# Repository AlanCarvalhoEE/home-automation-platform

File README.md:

# Home Automation Platform (HAP)

A modular, self-hosted home automation platform focused on reliability, local control, and secure remote access.

The system is designed around a Raspberry Pi server that centralizes application logic and device state, ESP8266-based IoT modules for field control, and a mobile
application as the primary user interface. Communication between components is event-driven and optimized for embedded and low-latency environments.

---

## System Architecture

The platform follows a layered architecture:

- **User Interface Layer**: Mobile and web-based interfaces for monitoring and
  control.
- **Application Layer**: Centralized logic running on a Raspberry Pi server.
- **Device Layer**: Custom ESP8266-based hardware modules controlling actuators
  and sensors.

Remote access is secured using a VPN, allowing the system to remain fully functional without relying on external cloud services.

---

## Components Overview

### Mobile App / Web Interface
- Provides real-time monitoring and control of devices
- Sends user commands to the server
- Displays device states and sensor data

### Server (Raspberry Pi)
- Central application logic
- Device state management
- Local database storage
- MQTT-based device communication
- REST API for configuration and user interfaces

### IoT Devices (ESP8266)
- Custom-designed hardware modules
- Event-driven communication using MQTT
- Designed as lightweight, replaceable nodes
- Examples:
  - On/Off relay modules
  - Sensor modules
  - Air conditioner control modules

---

## Repository Structure

```
hap/
├── docs/       # Documentation, diagrams, images
├── firmware/   # ESP8266 firmware for IoT modules
├── hardware/   # PCB designs, schematics, manufacturing files
├── mobile/     # Android application
├── server/     # Core server logic and services
└── README.md
```

---

## Technology Stack

### Embedded & Hardware
- ESP8266
- C / Arduino framework
- Custom PCB design

### Server
- Raspberry Pi
- Python
- MQTT
- SQLite
- TCP/IP networking

### Mobile
- Android (Java)
- Local and remote control support

### Communication & Security
- MQTT for device communication
- REST API for configuration and UI interaction
- VPN-based secure remote access
- Local-first architecture (no cloud dependency)

---

## Communication Model

- Devices publish state changes and sensor data via MQTT
- The server processes events and applies application logic
- Commands are sent back to devices via MQTT topics
- The mobile app interacts with the server through secure API calls

---

## System Setup Steps

- Install a lightweight Raspberry Pi OS:
  - Raspberry Pi OS Lite (recommended)
  - Enable SSH during installation
  - Configure a static local IP address

- Update the system:
```
sudo apt update
sudo apt upgrade -y
```

- Install and configure GIT:
```
sudo apt install git -y
```

- Clone the repository:
```
git clone https://github.com/AlanCarvalhoEE/hap.git
```

- Enter project folder:
```
cd hap
```

- Edit your credentials:
```
cp server/scripts/credentials_example.py server/scripts/credentials.py
nano server/scripts/credentials.py
```

- Run setup.sh:
```
cd setup
chmod +x setup.sh
./setup.sh
```
  - The script will install all the needed packages, dependencies and services.

- Configure Mosquitto:
```
sudo nano /etc/mosquitto/mosquitto.conf
```
  - Include to the end of the file:
  ```
  listener 1883
  allow_anonymous true
  ```

- Restart Mosquitto:
```
sudo systemctl restart mosquitto
```

- Connect to your ZeroTier network (must be previously created on web browser):
```
sudo zerotier-cli join <network_id>
```
  - After joining, the device must be allowed on the ZeroTier network dashboard.

- Reboot the Raspberry Pi:
```
sudo reboot now
```

---

## Current Status

- Core server architecture implemented
- Custom IoT ON-OFF module developed and tested
- Core Android application implemented
- Secure remote access functional

---

## Roadmap

Planned improvements:

- New custom IoT modules development
- Formal MQTT topic and message schema documentation
- Device auto-discovery and provisioning
- Improved fault tolerance and reconnection logic
- Automated testing for server-side logic
- Expanded mobile app features and UI refinement

---

## License

This project is currently intended for personal and educational use.
Licensing details may be defined in the future.

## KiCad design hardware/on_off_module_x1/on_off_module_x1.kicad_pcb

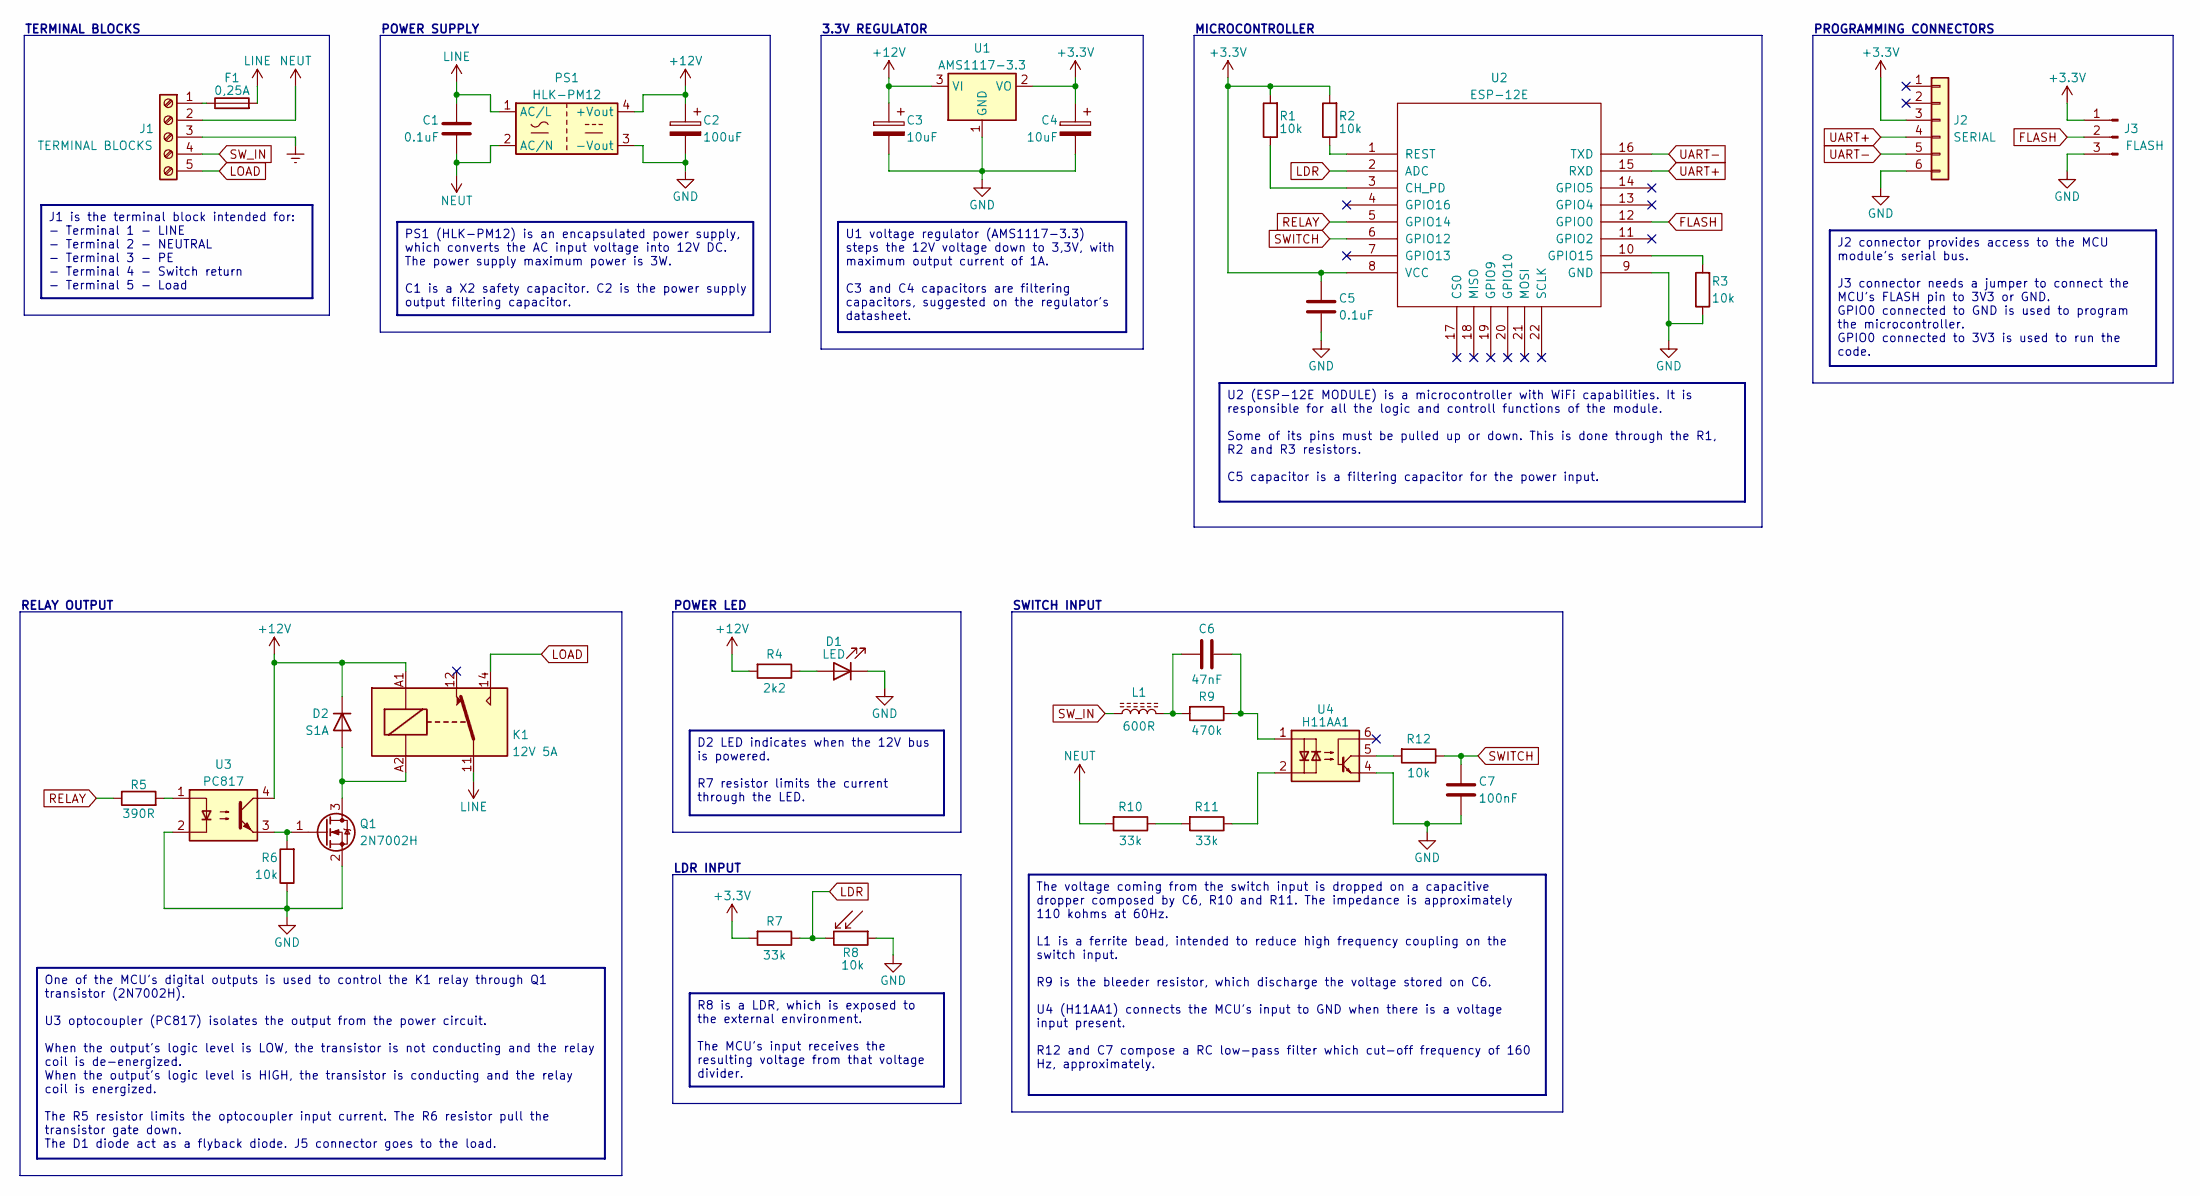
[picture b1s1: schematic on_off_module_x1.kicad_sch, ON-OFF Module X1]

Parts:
C1: 0.1uF; CAP_THT_CERAMIC_X2_18x6x15; Voltage 275V
C2: 100uF; CAP_SMD_ELEC_6.3x7.7; Voltage 16V
C3: 10uF; CAP_SMD_TANTALUM_CASE-A; Voltage 16V
C4: 10uF; CAP_SMD_TANTALUM_CASE-A; Voltage 6.3V
C5: 0.1uF; CAP_SMD_CERAMIC_0603; Voltage 6.3V
C6: 47nF; CAP_THT_CERAMIC_X2_13x5x11_P10; Voltage 350V
C7: 100nF; CAP_SMD_CERAMIC_0603; Voltage 6,3V
D1: LED; LED_SMD_0603
D2: S1A; DIODE_SMD_SMA
F1: 0,25A; FUSEHOLDER_THT_5x20_CLIP; Voltage 250V
J1: CONN_TERMINAL-BLOCK_5P_P5.08
J2: Conn_01x06_Socket; CONN_SOCKET-HEADER_1x06_V
J3: Conn_01x03_Socket; CONN_PIN-HEADER_1x03_V
K1: 12V 5A; RELAY_SPDT_FINDER_36.11
L1: 600R; BEAD_SMD_1206
PS1: HLK-PM12; HILINK_HLK-PMxx
Q1: 2N7002H; SOT-23
R1, R2, R3, R6, R12: 10k; RES_SMD_0603; Tolerance 5%
R4: 2k2; RES_SMD_0603; Tolerance 5%
R5: 390R; RES_SMD_0603; Tolerance 5%
R7: 33k; RES_SMD_0603; Tolerance 5%
R8: 10k; LDR_5_V
R9: 470k; RES_SMD_1206; Tolerance 5%
R10, R11: 33k; RES_SMD_1206; Tolerance 5%
U1: AMS1117-3.3; SOT-223-3_TAB2
U2: ESP-12E; MOD_ESP-12E
U3: PC817; SMDIP-4_7.62
U4: H11AA1; SMDIP-6_7.62

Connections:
+3.3V: C4.1, C5.2, J2.3, J3.1, R1.1, R2.1, R7.1, U1.2 (VO), U2.8 (VCC)
+12V: C2.1, C3.1, D2.1 (K), K1.A1, PS1.4 (+Vout), R4.1, U1.3 (VI), U3.4
Earth: J1.3
FLASH: J3.2, U2.12 (GPIO0)
GND: C2.2, C3.2, C4.2, C5.1, C7.2, D1.1 (K), J2.6, J3.3, PS1.3 (-Vout), Q1.2 (S), R3.2, R6.2, R8.1, U1.1 (GND), U2.9 (GND), U3.2, U4.4
LDR: R7.2, R8.2, U2.2 (ADC)
LINE: C1.1, F1.2, K1.11, PS1.1 (AC/L)
LOAD: J1.5, K1.14
NEUT: C1.2, J1.2, PS1.2 (AC/N), R10.1
unnamed: C6.1, L1.2, R9.1
unnamed: C6.2, R9.2, U4.1
unnamed: D1.2 (A), R4.2
unnamed: D2.2 (A), K1.A2, Q1.3 (D)
unnamed: F1.1, J1.1
unnamed: Q1.1 (G), R6.1, U3.3
unnamed: R5.1, U3.1
unnamed: R10.2, R11.1
unnamed: R11.2, U4.2
unnamed: R12.1, U4.5
unnamed: R1.2, U2.3 (CH_PD)
unnamed: R3.1, U2.10 (GPIO15)
unnamed: R2.2, U2.1 (REST)
RELAY: R5.2, U2.5 (GPIO14)
SWITCH: C7.1, R12.2, U2.6 (GPIO12)
SW_IN: J1.4, L1.1
UART+: J2.4, U2.15 (RXD)
UART-: J2.5, U2.16 (TXD)

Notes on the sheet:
PS1 (HLK-PM12) is an encapsulated power supply, which converts the AC input voltage into 12V DC. The power supply maximum power is 3W. C1 is a X2 safety capacitor. C2 is the power supply output filtering capacitor.
R8 is a LDR, which is exposed to the external environment. The MCU's input receives the resulting voltage from that voltage divider.
One of the MCU's digital outputs is used to control the K1 relay through Q1 transistor (2N7002H). U3 optocoupler (PC817) isolates the output from the power circuit. When the output's logic level is LOW, the transistor is not conducting and the relay coil is de-energized. When the output's logic lev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
J2 connector provides access to the MCU module's serial bus. J3 connector needs a jumper to connect the MCU's FLASH pin to 3V3 or GND. GPIO0 connected to GND is used to program the microcontroller. GPIO0 connected to 3V3 is used to run the code.
D2 LED indicates when the 12V bus is powered. R7 resistor limits the current through the LED.
U2 (ESP-12E MODULE) is a microcontroller with WiFi capabilities. It is responsible for all the logic and controll functions of the module. Some of its pins must be pulled up or down. This is done through the R1, R2 and R3 resistors. C5 capacitor is a filtering capacitor for the power input.
U1 voltage regulator (AMS1117-3.3) steps the 12V voltage down to 3,3V, with maximum output current of 1A. C3 and C4 capacitors are filtering capacitors, suggested on the regulator's datasheet.
J1 is the terminal block intended for: - Terminal 1 - LINE - Terminal 2 - NEUTRAL - Terminal 3 - PE - Terminal 4 - Switch return - Terminal 5 - Load
The voltage coming from the switch input is dropped on a capacitive dropper composed by C6, R10 and R11. The impedance is approximately 110 kohms at 60Hz. L1 is a ferrite bead, intended to reduce high frequency coupling on the switch input. R9 is the bleeder resistor, which discharge the voltage st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
PROGRAMMING CONNECTORS
RELAY OUTPUT
POWER LED
POWER SUPPLY
LDR INPUT
TERMINAL BLOCKS
SWITCH INPUT
MICROCONTROLLER
3.3V REGULATOR

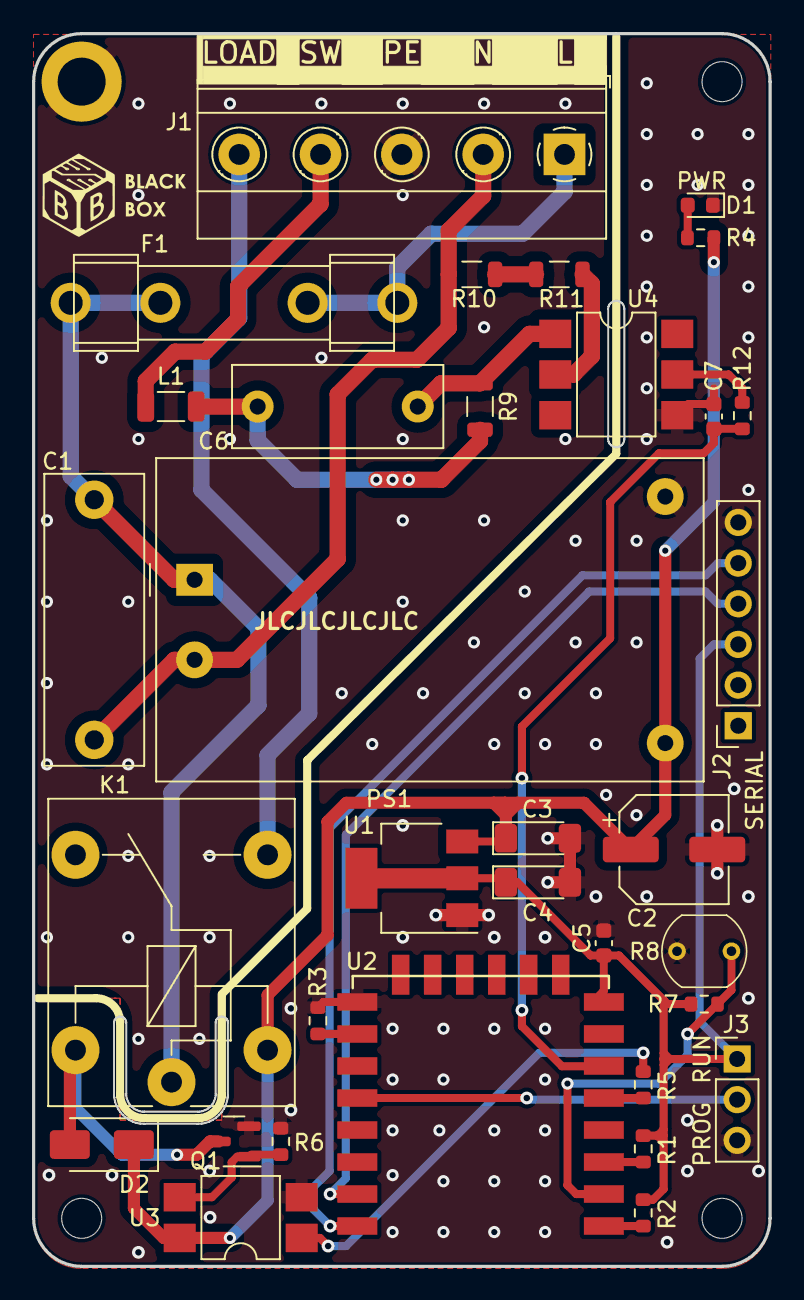
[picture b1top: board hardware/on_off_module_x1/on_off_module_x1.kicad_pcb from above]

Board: 2 copper layers, 46.0 x 77.0 mm, 33 parts (0 on the bottom side), 26 nets.

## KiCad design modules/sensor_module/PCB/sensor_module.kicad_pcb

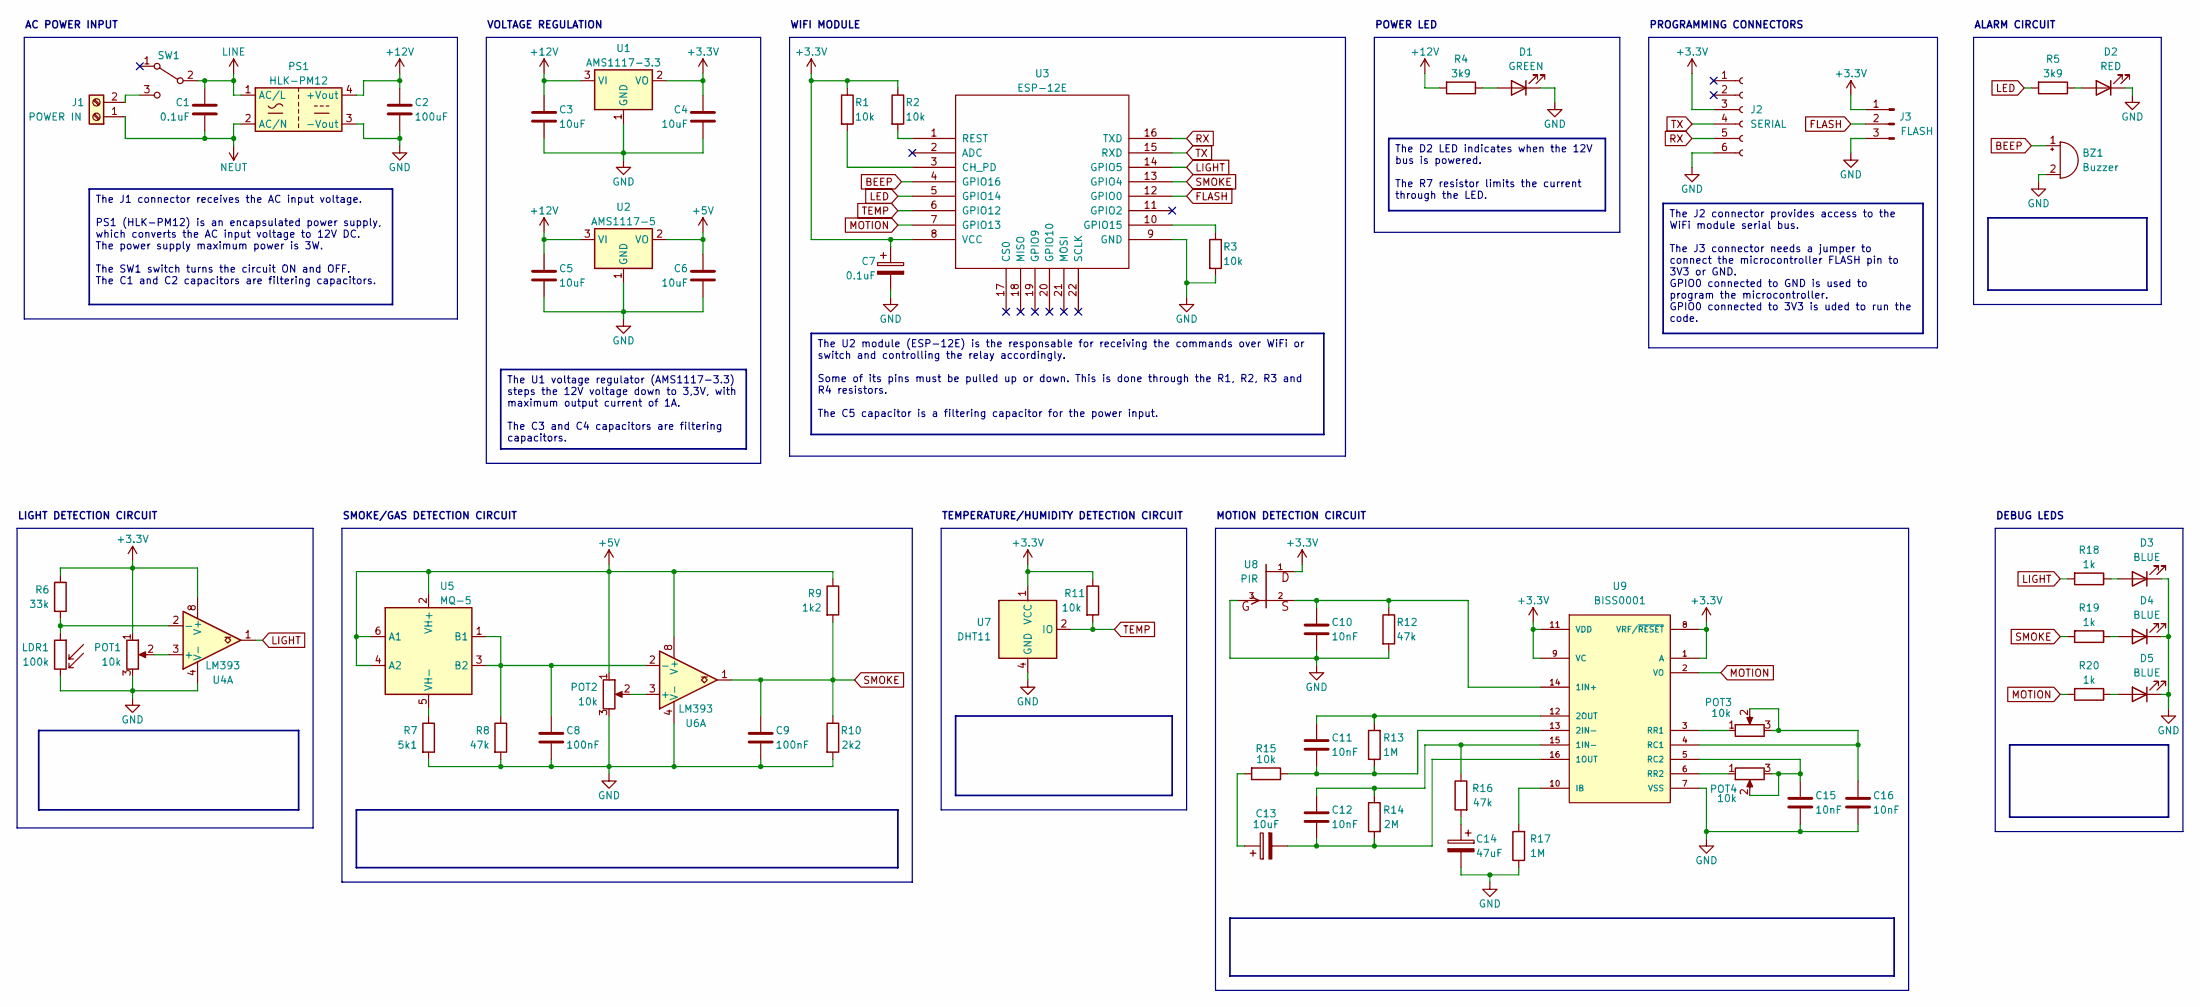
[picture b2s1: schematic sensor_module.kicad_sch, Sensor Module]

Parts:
BZ1: Buzzer; Buzzer_12x9.5RM7.6
C1: 0.1uF; C_Rect_L18.0mm_W6.0mm_P15.00mm_FKS3_FKP3; Voltage 275V
C2: 100uF; CP_Elec_6.3x7.7; Voltage 16V
C3, C5: 10uF; CP_EIA-3216-18_Kemet-A; Voltage 16V
C4, C6: 10uF; CP_EIA-3216-18_Kemet-A; Voltage 6.3V
C7: 0.1uF; C_0603_1608Metric; Voltage 6.3V
C8, C9: 100nF; C_0603_1608Metric; Voltage 16V
C10, C11, C12, C15, C16: 10nF; C_0603_1608Metric; Voltage 16V
C13: 10uF; CP_Elec_5x5.4
C14: 47uF; CP_Elec_5x5.4
D1: GREEN; LED_0603_1608Metric
D2: RED; LED_D3.0mm
D3, D4, D5: BLUE; LED_0603_1608Metric
J1: Screw_Terminal_01x02; TerminalBlock_Phoenix_MKDS-1,5-2-5.08_1x02_P5.08mm_Horizont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
J2: Conn_01x06_Socket; PinHeader_1x06_P2.54mm_Vertical
J3: Conn_01x03_Socket; PinSocket_1x03_P2.54mm_Vertical
LDR1: 100k; R_LDR_5.1x4.3mm_P3.4mm_Vertical
POT1, POT2, POT3, POT4: 10k; TRIM_3362P-1-103
PS1: HLK-PM12; Converter_ACDC_HiLink_HLK-PMxx
R1, R2, R3, R11, R15: 10k; R_0603_1608Metric; Tolerance 5%
R4, R5: 3k9; R_0603_1608Metric; Tolerance 5%
R6: 33k; R_0603_1608Metric; Tolerance 5%
R7: 5k1; R_0603_1608Metric; Tolerance 5%
R8, R12, R16: 47k; R_0603_1608Metric; Tolerance 5%
R9: 1k2; R_0603_1608Metric; Tolerance 5%
R10: 2k2; R_0603_1608Metric; Tolerance 5%
R13, R17: 1M; R_0603_1608Metric; Tolerance 5%
R14: 2M; R_0603_1608Metric; Tolerance 5%
R18, R19, R20: 1k; R_0603_1608Metric; Tolerance 5%
SW1: SW_SPDT; Toggle_Switch_SelfLocking_7x7
U1: AMS1117-3.3; SOT-223-3_TabPin2
U2: AMS1117-5; SOT-223-3_TabPin2
U3: ESP-12E; ESP-12E_SMD
U4, U6: LM393; SOIC-8-1EP_3.9x4.9mm_P1.27mm_EP2.62x3.51mm
U5: MQ-5; MQ-6
U7: DHT11; SNR4-2.54-15.5X12.0X5.5MM
U8: PIR; TO5
U9: BISS0001; SOIC127P600X180-16N

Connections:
+3.3V: C4.1, C7.1, J2.3, J3.1, POT1.1, R1.1, R2.1, R6.1, R11.1, U1.2 (VO), U3.8 (VCC), U4.8 (V+), U7.1 (VCC), U8.1, U9.1 (A), U9.8 (VRF/~RESET), U9.9 (VC), U9.11 (VDD)
+5V: C6.1, POT2.1, R9.1, U2.2 (VO), U5.2 (VH+), U5.4 (A2), U5.6 (A1), U6.8 (V+)
+12V: C2.1, C3.1, C5.1, PS1.4 (+Vout), R4.2, U1.3 (VI), U2.3 (VI)
BEEP: BZ1.1 (-), U3.4 (GPIO16)
FLASH: J3.2, U3.12 (GPIO0)
GND: BZ1.2 (+), C2.2, C3.2, C4.2, C5.2, C6.2, C7.2, C8.2, C9.2, C10.2, C14.2, C15.2, C16.2, D1.1 (K), D2.1 (K), D3.1 (K), D4.1 (K), D5.1 (K), J2.6, J3.3, LDR1.2, POT1.3, POT2.3, PS1.3 (-Vout), R3.2, R7.2, R8.2, R10.2, R12.2, R17.1, U1.1 (GND), U2.1 (GND), U3.9 (GND), U4.4 (V-), U6.4 (V-), U7.4 (GND), U8.3, U9.7 (VSS)
LED: R5.2, U3.5 (GPIO14)
LIGHT: R18.2, U3.14 (GPIO5), U4.1
LINE: C1.1, PS1.1 (AC/L), SW1.2 (B)
MOTION: R20.2, U3.7 (GPIO13), U9.2 (VO)
NEUT: C1.2, J1.1, PS1.2 (AC/N)
unnamed: C13.1, R15.2
unnamed: C14.1, R16.2
unnamed: D1.2 (A), R4.1
unnamed: D2.2 (A), R5.1
unnamed: D3.2 (A), R18.1
unnamed: D4.2 (A), R19.1
unnamed: D5.2 (A), R20.1
unnamed: J1.2, SW1.3 (C)
unnamed: R1.2, U3.3 (CH_PD)
unnamed: R3.1, U3.10 (GPIO15)
unnamed: R2.2, U3.1 (REST)
unnamed: POT1.2, U4.3 (+)
unnamed: LDR1.1, R6.2, U4.2 (-)
unnamed: C8.1, R8.1, U5.1 (B1), U5.3 (B2), U6.2 (-)
unnamed: R7.1, U5.5 (VH-)
unnamed: POT2.2, U6.3 (+)
unnamed: C10.1, R12.1, U8.2, U9.14 (1IN+)
unnamed: C12.2, R14.1, R16.1, U9.15 (1IN-)
unnamed: C12.1, C13.2, R14.2, U9.16 (1OUT)
unnamed: C11.2, R13.1, R15.1, U9.13 (2IN-)
unnamed: C11.1, R13.2, U9.12 (2OUT)
unnamed: R17.2, U9.10 (IB)
unnamed: C16.1, POT3.2, POT3.3, U9.4 (RC1)
unnamed: C15.1, POT4.2, POT4.3, U9.5 (RC2)
unnamed: POT3.1, U9.3 (RR1)
unnamed: POT4.1, U9.6 (RR2)
RX: J2.5, U3.16 (TXD)
SMOKE: C9.1, R9.2, R10.1, R19.2, U3.13 (GPIO4), U6.1
TEMP: R11.2, U3.6 (GPIO12), U7.2 (IO)
TX: J2.4, U3.15 (RXD)

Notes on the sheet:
The J1 connector receives the AC input voltage. PS1 (HLK-PM12) is an encapsulated power supply, which converts the AC input voltage to 12V DC. The power supply maximum power is 3W. The SW1 switch turns the circuit ON and OFF. The C1 and C2 capacitors are filtering capacitors.
The J2 connector provides access to the WiFi module serial bus. The J3 connector needs a jumper to connect the microcontroller FLASH pin to 3V3 or GND. GPIO0 connected to GND is used to program the microcontroller. GPIO0 connected to 3V3 is uded to run the code.
The D2 LED indicates when the 12V bus is powered. The R7 resistor limits the current through the LED.
The U2 module (ESP-12E) is the responsable for receiving the commands over WiFi or switch and controlling the relay accordingly. Some of its pins must be pulled up or down. This is done through the R1, R2, R3 and R4 resistors. The C5 capacitor is a filtering capacitor for the power input.
The U1 voltage regulator (AMS1117-3.3) steps the 12V voltage down to 3,3V, with maximum output current of 1A. The C3 and C4 capacitors are filtering capacitors.
PROGRAMMING CONNECTORS
POWER LED
LIGHT DETECTION CIRCUIT
AC POWER INPUT
MOTION DETECTION CIRCUIT
DEBUG LEDS
SMOKE/GAS DETECTION CIRCUIT
ALARM CIRCUIT
WIFI MODULE
VOLTAGE REGULATION
TEMPERATURE/HUMIDITY DETECTION CIRCUIT

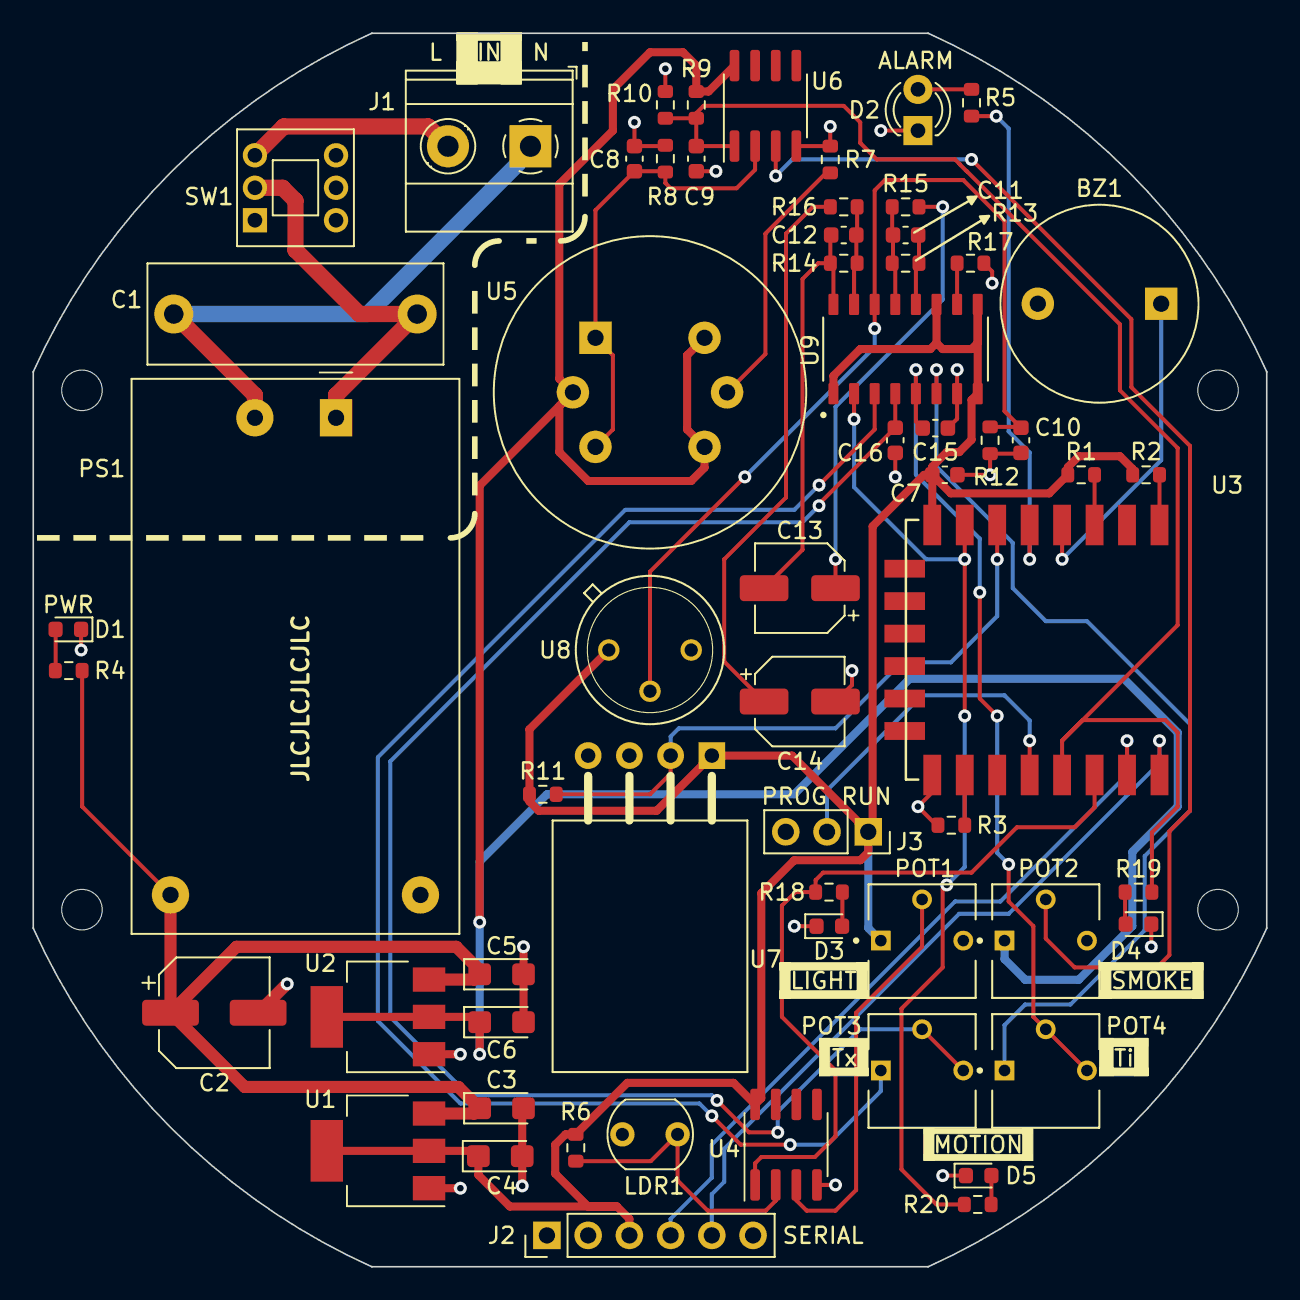
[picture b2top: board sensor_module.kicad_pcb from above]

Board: 2 copper layers, 76.0 x 76.0 mm, 61 parts (0 on the bottom side), 41 nets.

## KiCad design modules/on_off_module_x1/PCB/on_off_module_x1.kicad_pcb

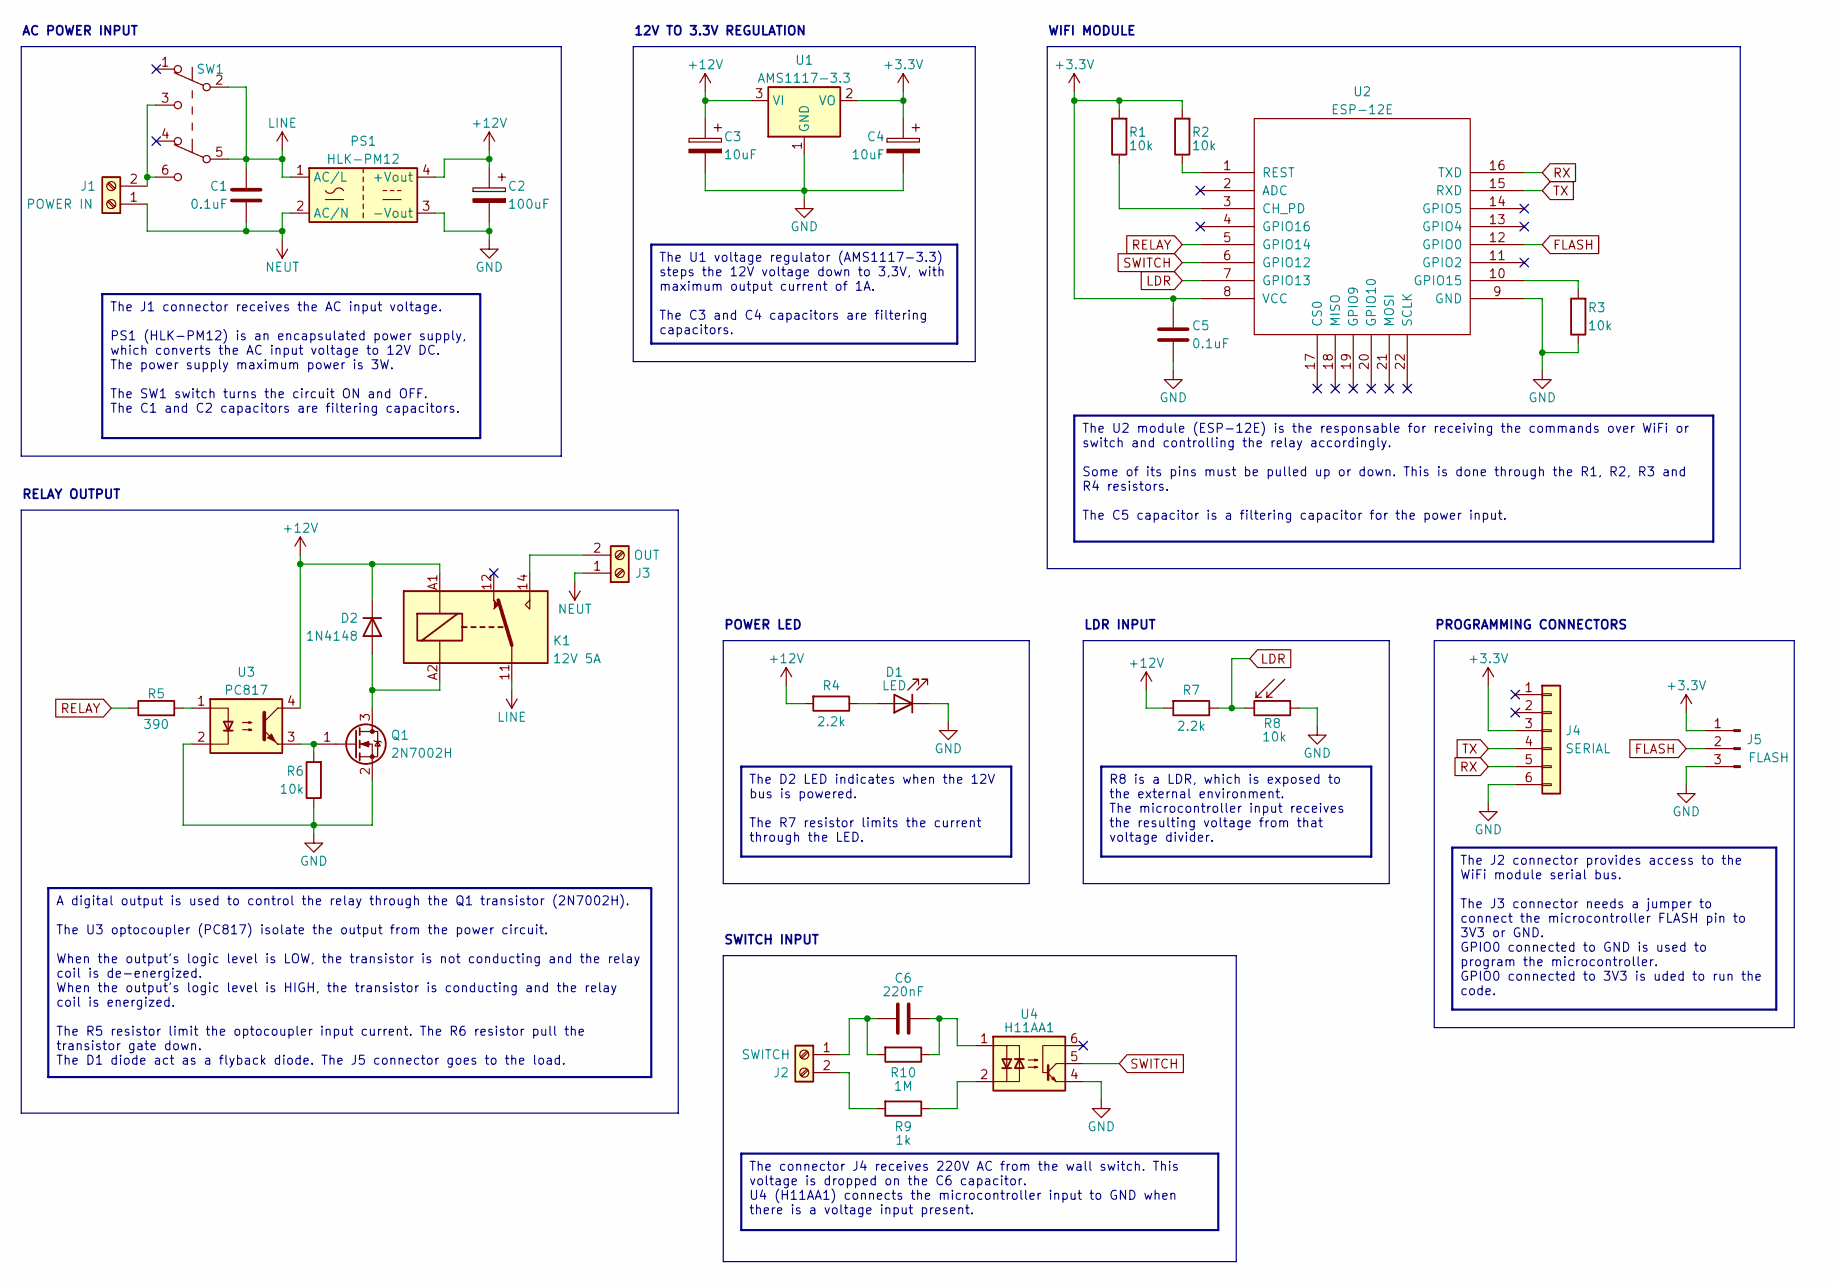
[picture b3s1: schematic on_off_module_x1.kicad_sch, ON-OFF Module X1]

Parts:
C1: 0.1uF; CAP_THT_CERAMIC_X2_18x6x15; Voltage 275V
C2: 100uF; CAP_SMD_ELEC_6.3x7.7; Voltage 16V
C3: 10uF; CAP_SMD_TANTALUM_CASE-A; Voltage 16V
C4: 10uF; CAP_SMD_TANTALUM_CASE-A; Voltage 6.3V
C5: 0.1uF; CAP_SMD_CERAMIC_0603; Voltage 6.3V
C6: 220nF; CAP_THT_CERAMIC_X2_13x6x12
D1: LED; LED_SMD_0603
D2: 1N4148; DIODE_SMD_SOD323F
J1, J2, J3: Screw_Terminal_01x02; CONN_TERMINAL-BLOCK_2P_P5.08
J4: Conn_01x06_Socket; CONN_SOCKET-HEADER_1x06_V
J5: Conn_01x03_Socket; CONN_PIN-HEADER_1x03_V
K1: 12V 5A; RELAY_SPDT_FINDER_36.11
PS1: HLK-PM12; HILINK_HLK-PMxx
Q1: 2N7002H; SOT-23
R1, R2, R3, R6: 10k; RES_SMD_0603; Tolerance 5%
R4, R7: 2.2k; RES_SMD_0603; Tolerance 5%
R5: 390; RES_SMD_0603; Tolerance 5%
R8: 10k; LDR_5_V
R9: 1k; RES_SMD_1206
R10: 1M; RES_SMD_1206
SW1: SW_SPDT; SW_TOGGLE_DPDT_THT_7x7
U1: AMS1117-3.3; SOT-223-3_TAB2
U2: ESP-12E; MOD_ESP-12E
U3: PC817; SMDIP-4_7.62
U4: H11AA1; SMDIP-6_7.62

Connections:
+3.3V: C4.1, C5.2, J4.3, J5.1, R1.1, R2.1, U1.2 (VO), U2.8 (VCC)
+12V: C2.1, C3.1, D2.1 (K), K1.A1, PS1.4 (+Vout), R4.1, R7.1, U1.3 (VI), U3.4
FLASH: J5.2, U2.12 (GPIO0)
GND: C2.2, C3.2, C4.2, C5.1, D1.1 (K), J4.6, J5.3, PS1.3 (-Vout), Q1.2 (S), R3.2, R6.2, R8.1, U1.1 (GND), U2.9 (GND), U3.2, U4.4
LDR: R7.2, R8.2, U2.7 (GPIO13)
LINE: C1.1, K1.11, PS1.1 (AC/L), SW1.2 (B), SW1.5 (B)
NEUT: C1.2, J1.1, J3.1, PS1.2 (AC/N)
unnamed: C6.2, R10.2, U4.1
unnamed: D1.2 (A), R4.2
unnamed: D2.2 (A), K1.A2, Q1.3 (D)
unnamed: J1.2, SW1.3 (C), SW1.6 (C)
unnamed: C6.1, J2.1, R10.1
unnamed: J2.2, R9.1
unnamed: J3.2, K1.14
unnamed: Q1.1 (G), R6.1, U3.3
unnamed: R5.1, U3.1
unnamed: R9.2, U4.2
unnamed: R1.2, U2.3 (CH_PD)
unnamed: R3.1, U2.10 (GPIO15)
unnamed: R2.2, U2.1 (REST)
RELAY: R5.2, U2.5 (GPIO14)
RX: J4.5, U2.16 (TXD)
SWITCH: U2.6 (GPIO12), U4.5
TX: J4.4, U2.15 (RXD)

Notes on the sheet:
The J1 connector receives the AC input voltage. PS1 (HLK-PM12) is an encapsulated power supply, which converts the AC input voltage to 12V DC. The power supply maximum power is 3W. The SW1 switch turns the circuit ON and OFF. The C1 and C2 capacitors are filtering capacitors.
R8 is a LDR, which is exposed to the external environment. The microcontroller input receives the resulting voltage from that voltage divider.
A digital output is used to control the relay through the Q1 transistor (2N7002H). The U3 optocoupler (PC817) isolate the output from the power circuit. When the output's logic level is LOW, the transistor is not conducting and the relay coil is de-energized. When the output's logic level is HIGH, 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
The J2 connector provides access to the WiFi module serial bus. The J3 connector needs a jumper to connect the microcontroller FLASH pin to 3V3 or GND. GPIO0 connected to GND is used to program the microcontroller. GPIO0 connected to 3V3 is uded to run the code.
The D2 LED indicates when the 12V bus is powered. The R7 resistor limits the current through the LED.
The U2 module (ESP-12E) is the responsable for receiving the commands over WiFi or switch and controlling the relay accordingly. Some of its pins must be pulled up or down. This is done through the R1, R2, R3 and R4 resistors. The C5 capacitor is a filtering capacitor for the power input.
The U1 voltage regulator (AMS1117-3.3) steps the 12V voltage down to 3,3V, with maximum output current of 1A. The C3 and C4 capacitors are filtering capacitors.
The connector J4 receives 220V AC from the wall switch. This voltage is dropped on the C6 capacitor. U4 (H11AA1) connects the microcontroller input to GND when there is a voltage input present.
PROGRAMMING CONNECTORS
RELAY OUTPUT
POWER LED
AC POWER INPUT
LDR INPUT
SWITCH INPUT
WIFI MODULE
12V TO 3.3V REGULATION

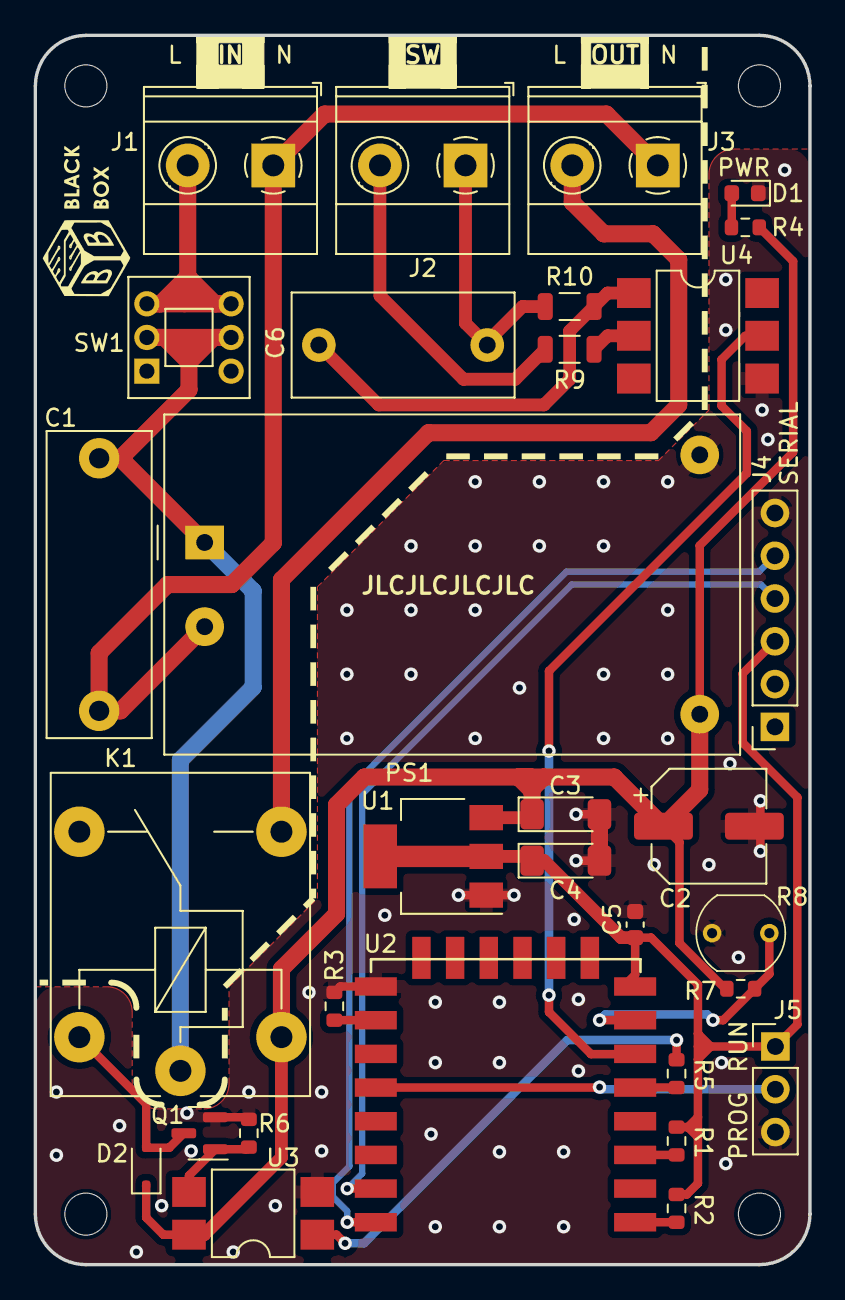
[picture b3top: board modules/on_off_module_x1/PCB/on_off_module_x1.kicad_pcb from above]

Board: 2 copper layers, 46.0 x 73.0 mm, 31 parts (0 on the bottom side), 24 nets.
